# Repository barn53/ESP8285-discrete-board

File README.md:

# ESP8285 discrete board
 Test board with discrete ESP8285 and CP2104 ICs

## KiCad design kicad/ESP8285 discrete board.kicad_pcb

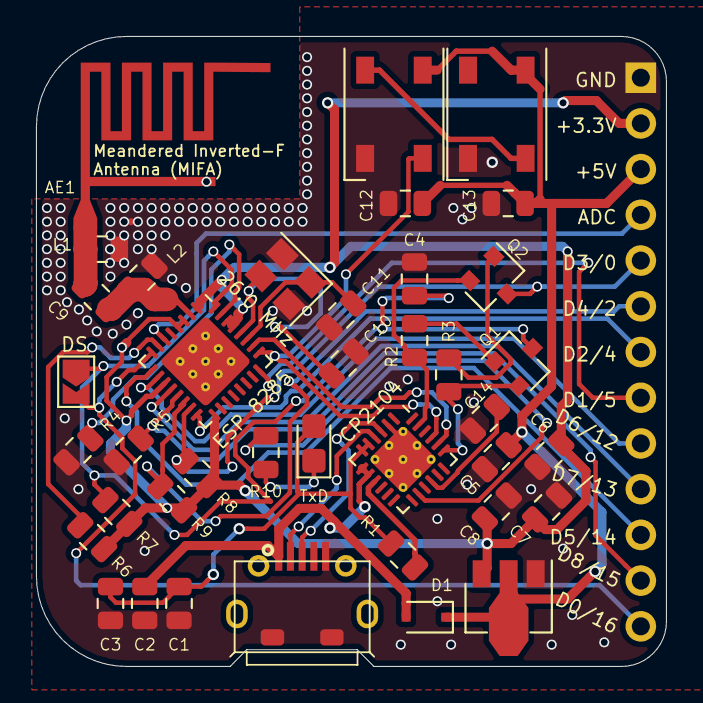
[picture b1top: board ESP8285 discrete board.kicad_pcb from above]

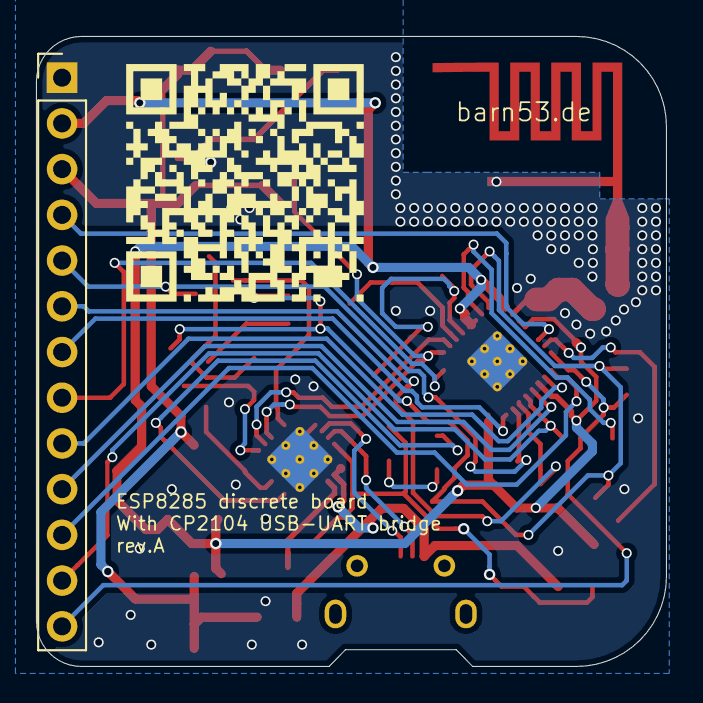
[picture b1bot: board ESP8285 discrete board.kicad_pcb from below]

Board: 2 copper layers, 35.0 x 35.0 mm, 41 parts (2 on the bottom side), 35 nets.

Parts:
AE1: PCB_Antenna_2.4GHz_1mm; PCB_Antenna_2.4GHz_MIFA_Layout_1mm_FR4_PCB
C1, C4, C6, C12, C13: 100n; C_0805_2012Metric
C2, C5, C7: 1u; C_0805_2012Metric
C3: 4u7; C_0805_2012Metric
C8: 10u; C_0805_2012Metric
C9: 5.6p; C_0805_2012Metric
C10, C11: 10p; C_0805_2012Metric
C14: 4.7u; C_0805_2012Metric
D1: BAT60A; D_SOD-323F
D2, D3: WS2812B; LED_WS2812B_PLCC4_5.0x5.0mm_P3.2mm
D4: TxD; LED_0805_2012Metric_Castellated
J1: USB_B_Micro; MicroUSB_through_hole_fixing
J2: Conn_01x13; PinHeader_1x13_P2.54mm_Vertical
JP1: DeepSleep Wakeup; SolderJumper-2_P1.3mm_Open_Masked_TrianglePad1.0x1.5mm
L1, L2: L; L_0805_2012Metric
Q1, Q2: S8050_J3Y; SOT-23
QR*****: ESP8285-discrete-board
R1: 4k7; R_0805_2012Metric
R2, R3, R5, R6, R7, R8, R9: 10k; R_0805_2012Metric
R4: 12k ±1%; R_0805_2012Metric
R10: 270; R_0805_2012Metric
U1: CP2104; QFN-24-1EP_4x4mm_P0.5mm_EP2.7x2.7mm_ThermalVias
U2: BL8565; SOT-89-3
U3: ESP_8285; QFN-32-1EP_5x5mm_P0.5mm_EP3.6x3.6mm_ThermalVias
Y1: 26.0 MHz; Crystal_SMD_3225-4Pin_3.2x2.5mm

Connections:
+3V3: C6.1, C7.1, C8.1, J2.2, R6.1, R7.1, R8.1, R9.1, U2.3, U3.1, U3.3, U3.4, U3.11, U3.17, U3.29, U3.30
+5V: C5.1, C12.1, C13.1, D1.1, D2.1, D3.1, J2.3, U2.2
/Connections/ADC: J2.4, U3.6
/Connections/GPIO2: J2.6, R9.2, U3.14
/Connections/GPIO4: J2.7, U3.16
/Connections/GPIO5: J2.8, U3.24
/Connections/GPIO12: J2.9, U3.10
/Connections/GPIO13: J2.10, U3.12
/Connections/GPIO14: J2.11, U3.9
/Connections/GPIO15: J2.12, R5.1, U3.13
/Connections/GPIO16: J2.13, JP1.2, U3.8
/ESP8285/ANT: AE1.1, C9.2, L1.1
/ESP8285/Enable: R6.2, U3.7
/ESP8285/LNA: C9.1, L2.1, U3.2
/ESP8285/Reset: C4.1, JP1.1, Q1.3, R7.2, U3.32
/ESP8285/XTAL_IN: C10.1, U3.28, Y1.3
/ESP8285/XTAL_OUT: C11.1, U3.27, Y1.1
/GPIO0: J2.5, Q2.3, R8.2, U3.15
/Power/D+: J1.3, U1.3
/Power/D-: J1.2, U1.4
/Power/VBus: C2.1, D1.2, J1.1, U1.7, U1.8
/USB_UART/DTR: Q2.2, R2.2, U1.23
/USB_UART/GPIO.0: R10.2, U1.14
/USB_UART/RTS: Q1.2, R3.2, U1.19
/USB_UART/RxD: U1.20, U3.26
/USB_UART/VDD: C1.1, C3.1, D4.2, R1.1, U1.5, U1.6
/WS2812/DIn: D2.4, U1.21, U3.25
GND: AE1.2, C1.2, C2.2, C3.2, C4.2, C5.2, C6.2, C7.2, C8.2, C10.2, C11.2, C12.2, C13.2, C14.2, D2.3, D3.3, J1.5, J1.6, J2.1, L1.2, L2.2, R4.2, R5.2, U1.2, U1.25, U2.1, U3.33, Y1.2, Y1.4
unnamed: C14.1, U1.16
unnamed: D2.2, D3.4
unnamed: D4.1, R10.1
unnamed: Q1.1, R2.1
unnamed: Q2.1, R3.1
unnamed: R1.2, U1.9
unnamed: R4.1, U3.31

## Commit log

2019-12-18 This might be the first fabrication commit (rev.A)
2019-12-18 Add Blender file and change fabrication output folder
2020-01-07 Periodical commit
2020-01-07 Inverted notation
2020-02-04 saving commit
2021-01-19 minor
